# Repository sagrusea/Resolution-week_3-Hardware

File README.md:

# Resolution-week_3-Hardware
A cross made up of 16 leds with another 4 leds, one for each corner. I made this becouse i wanted to use the cd4020 and lm556 for the first time, and also create a good looking circuit.

#### Render:

#### Schematic:

#### KiCanvas:  
<a href="https://kicanvas.org/?repo=https%3A%2F%2Fgithub.com%2Fsagrusea%2FResolution-week_3-Hardware%2Ftree%2Fmain%2Fsrc%2FKiCad">link</a>

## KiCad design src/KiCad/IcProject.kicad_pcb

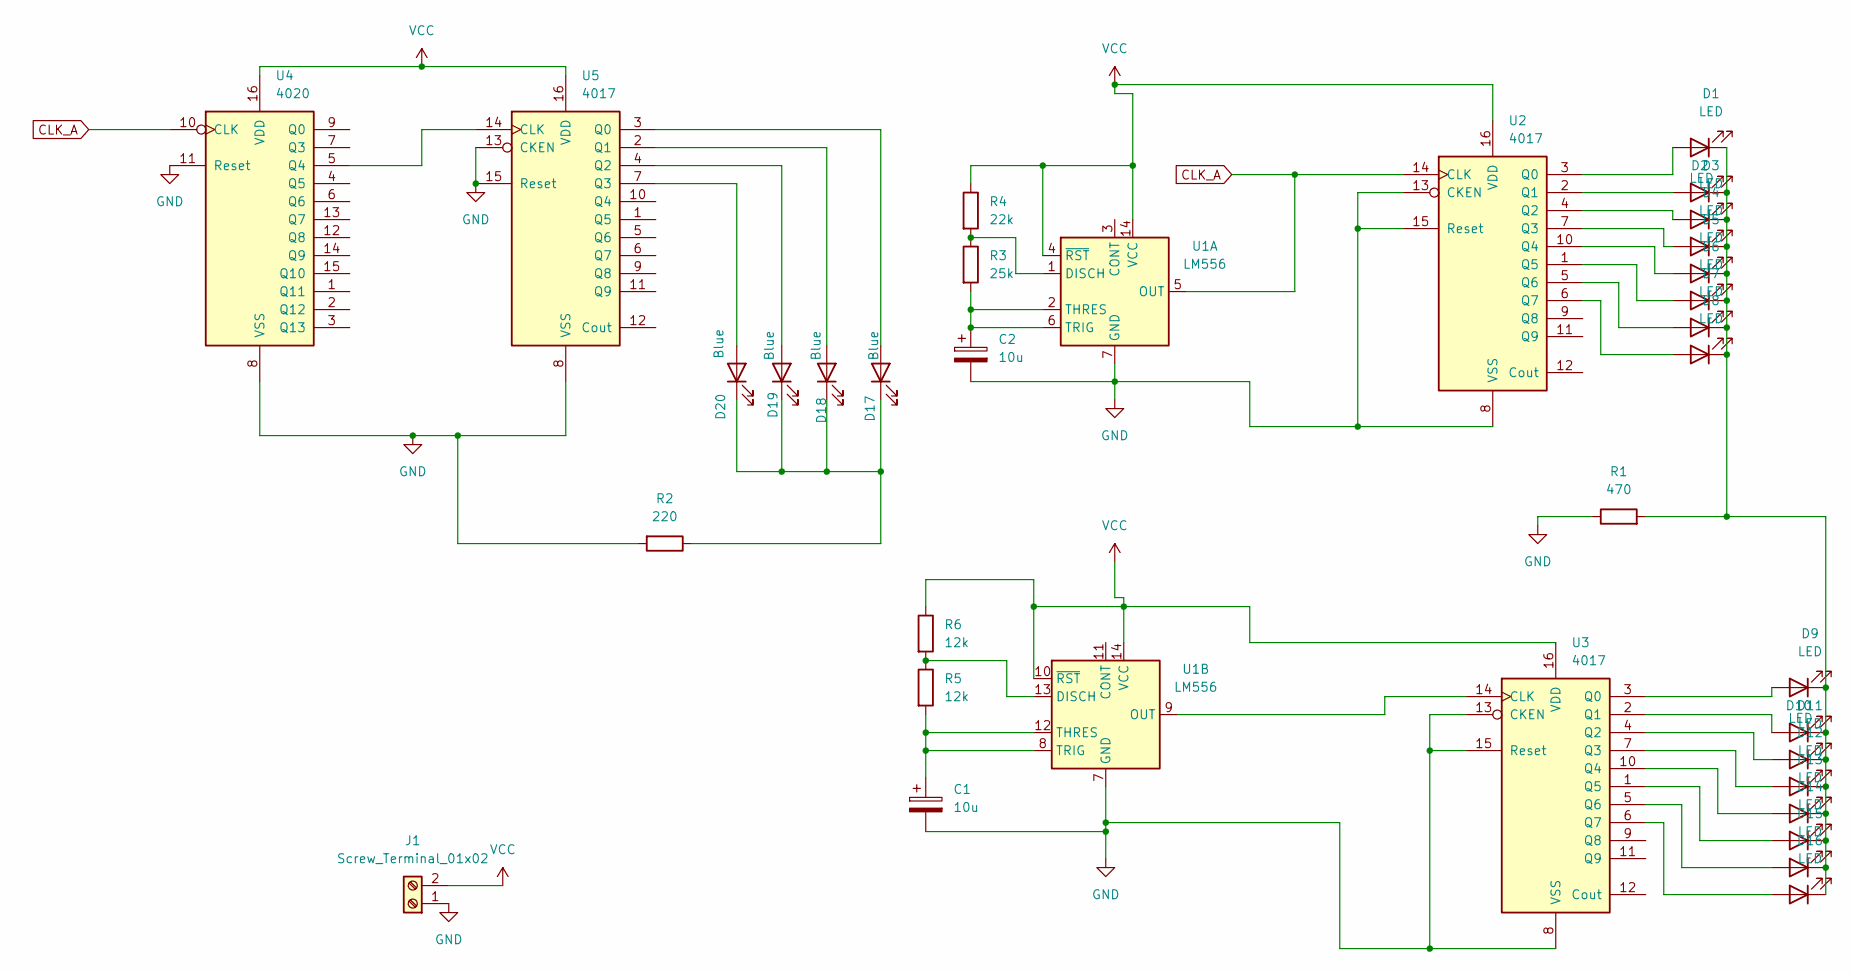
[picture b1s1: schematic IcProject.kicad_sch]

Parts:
C1, C2: 10u; CP_Radial_D5.0mm_P2.00mm
D1, D2, D3, D4, D5, D6, D7, D8, D9, D10, D11, D12, D13, D14, D15, D16: LED; LED_D3.0mm
D17, D18, D19, D20: Blue; LED_D3.0mm
J1: Screw_Terminal_01x02; TerminalBlock_MaiXu_MX126-5.0-02P_1x02_P5.00mm
R1: 470; R_Axial_DIN0207_L6.3mm_D2.5mm_P7.62mm_Horizontal
R2: 220; R_Axial_DIN0207_L6.3mm_D2.5mm_P7.62mm_Horizontal
R3: 25k; R_Axial_DIN0207_L6.3mm_D2.5mm_P7.62mm_Horizontal
R4: 22k; R_Axial_DIN0207_L6.3mm_D2.5mm_P7.62mm_Horizontal
R5, R6: 12k; R_Axial_DIN0207_L6.3mm_D2.5mm_P7.62mm_Horizontal
U1: LM556; DIP-14_W7.62mm
U2, U3, U5: 4017; DIP-16_W7.62mm
U4: 4020; DIP-16_W7.62mm

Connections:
CLK_A: U1.5 (OUT), U2.14 (CLK), U4.10 (CLK)
GND: C1.2, C2.2, J1.1, R1.1, R2.2, U1.7 (GND), U2.8 (VSS), U2.13 (CKEN), U2.15 (Reset), U3.8 (VSS), U3.13 (CKEN), U3.15 (Reset), U4.8 (VSS), U4.11 (Reset), U5.8 (VSS), U5.13 (CKEN), U5.15 (Reset)
unnamed: D1.2 (A), U2.3 (Q0)
unnamed: D1.1 (K), D2.1 (K), D3.1 (K), D4.1 (K), D5.1 (K), D6.1 (K), D7.1 (K), D8.1 (K), D9.1 (K), D10.1 (K), D11.1 (K), D12.1 (K), D13.1 (K), D14.1 (K), D15.1 (K), D16.1 (K), R1.2
unnamed: D2.2 (A), U2.2 (Q1)
unnamed: D3.2 (A), U2.4 (Q2)
unnamed: D4.2 (A), U2.7 (Q3)
unnamed: D5.2 (A), U2.10 (Q4)
unnamed: D6.2 (A), U2.1 (Q5)
unnamed: D7.2 (A), U2.5 (Q6)
unnamed: D8.2 (A), U2.6 (Q7)
unnamed: D9.2 (A), U3.3 (Q0)
unnamed: D10.2 (A), U3.2 (Q1)
unnamed: D11.2 (A), U3.4 (Q2)
unnamed: D12.2 (A), U3.7 (Q3)
unnamed: D13.2 (A), U3.10 (Q4)
unnamed: D14.2 (A), U3.1 (Q5)
unnamed: D15.2 (A), U3.5 (Q6)
unnamed: D16.2 (A), U3.6 (Q7)
unnamed: D17.2 (A), U5.3 (Q0)
unnamed: D17.1 (K), D18.1 (K), D19.1 (K), D20.1 (K), R2.1
unnamed: D18.2 (A), U5.2 (Q1)
unnamed: D19.2 (A), U5.4 (Q2)
unnamed: D20.2 (A), U5.7 (Q3)
unnamed: R3.1, R4.2, U1.1 (DISCH)
unnamed: C2.1, R3.2, U1.2 (THRES), U1.6 (TRIG)
unnamed: R5.1, R6.2, U1.13 (DISCH)
unnamed: U1.9 (OUT), U3.14 (CLK)
unnamed: C1.1, R5.2, U1.8 (TRIG), U1.12 (THRES)
unnamed: U4.5 (Q4), U5.14 (CLK)
VCC: J1.2, R4.1, R6.1, U1.4 (~RST), U1.10 (~RST), U1.14 (VCC), U2.16 (VDD), U3.16 (VDD), U4.16 (VDD), U5.16 (VDD)

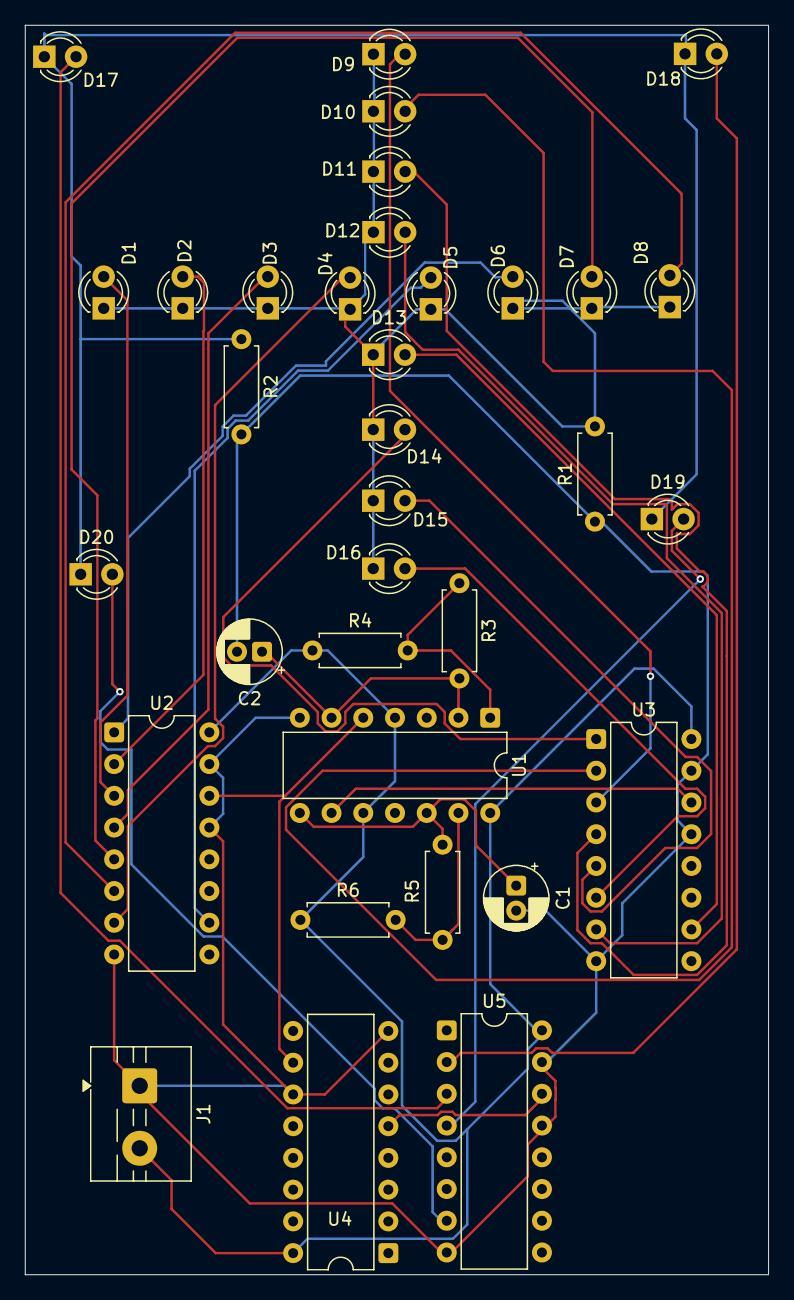
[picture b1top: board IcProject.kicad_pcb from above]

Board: 2 copper layers, 59.5 x 100.0 mm, 34 parts (0 on the bottom side), 31 nets.

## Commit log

2026-04-02 journaled
2026-06-05 updated the layout
